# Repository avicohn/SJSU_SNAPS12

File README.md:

SJSU_SNAPS12
============

Nanosatellite System Software developed by the 2012 - 2013 SJSU SNAPS team in collaboration with NASA Ames

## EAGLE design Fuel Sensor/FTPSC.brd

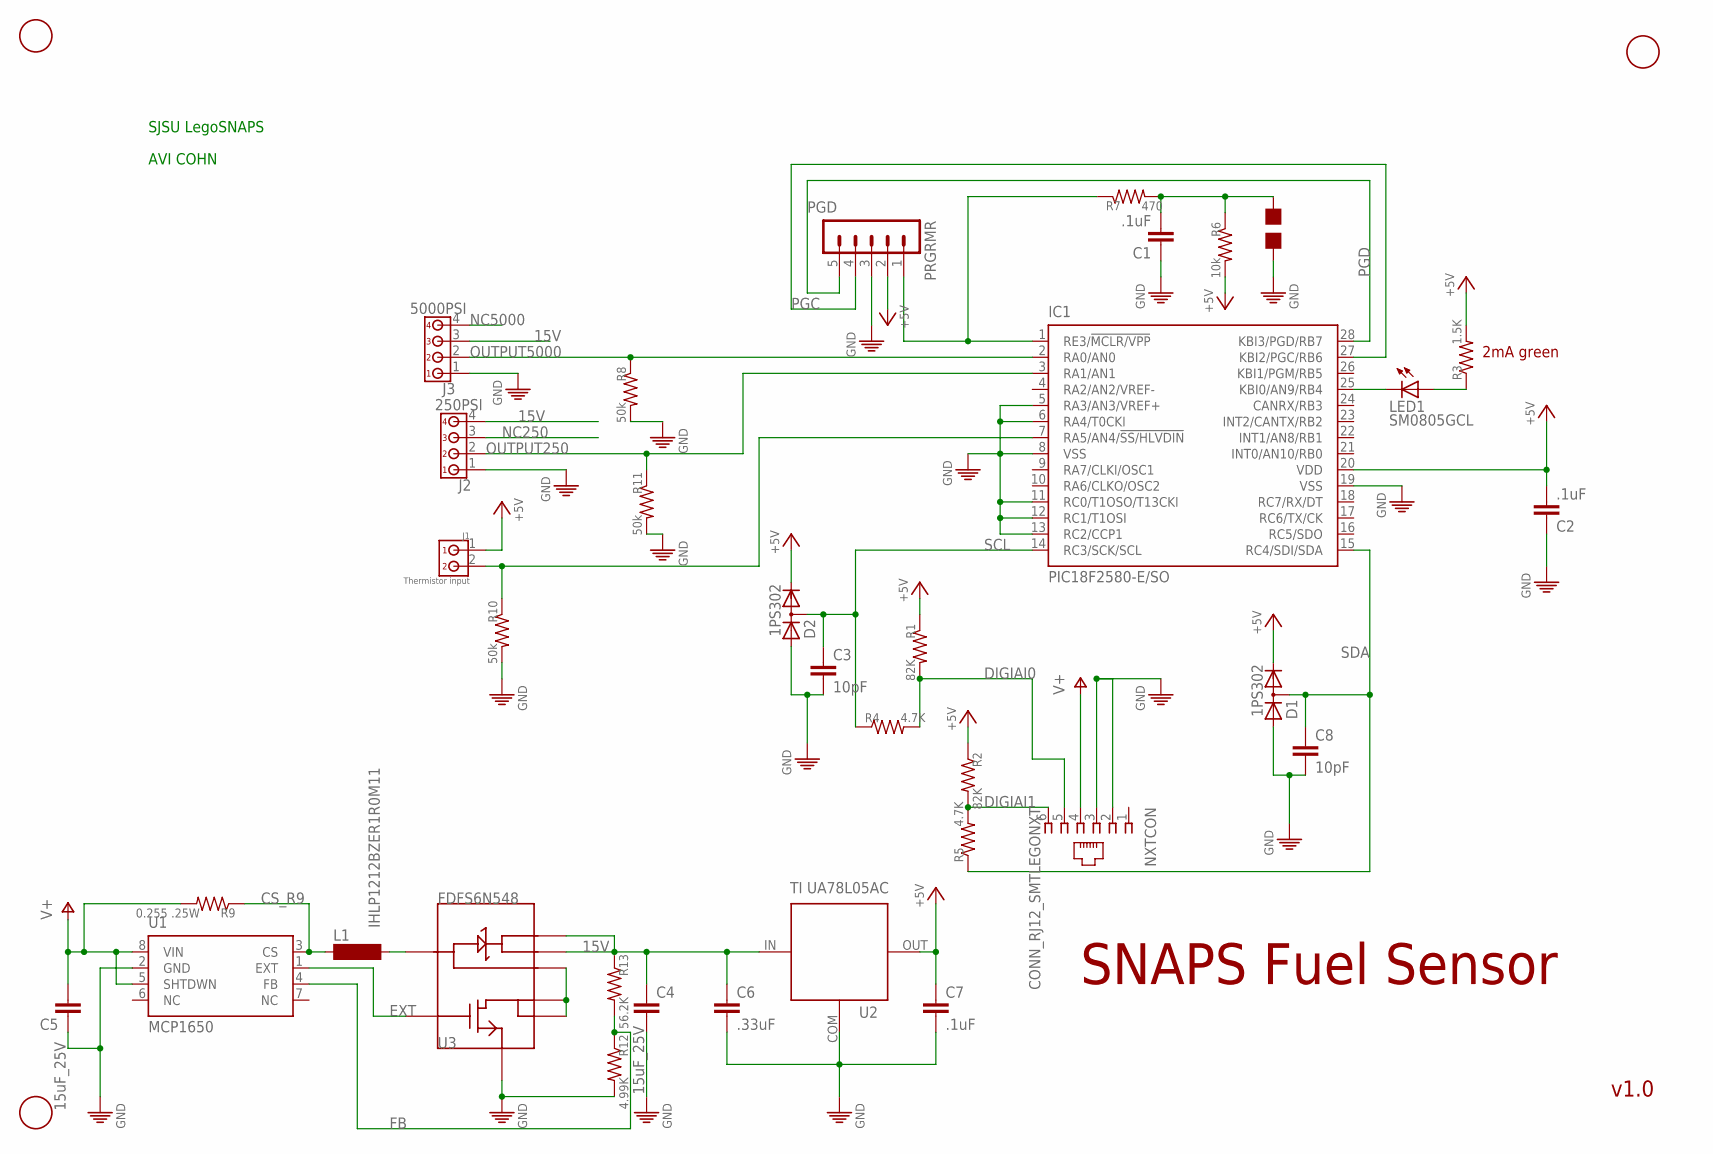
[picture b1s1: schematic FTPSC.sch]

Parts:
C1, C2, C7: .1uF; RCL_C0805
C3, C8: 10pF; RCL_C0805
C4, C5: 15uF_25V; RCL_C0805
C6: .33uF; RCL_C0805
D1, D2: 1PS302; SC70-3-R
IC1: PIC18F2580-E/SO; SO28W
J1: Thermistor input; CON-MOLEX_22-23-2021
J2: 250PSI; CON-MOLEX_22-23-2041
J3: 5000PSI; CON-MOLEX_22-23-2041
L1: IHLP1212BZER1R0M11; MS42
LED1: SM0805GCL; D0805
NXTCON: CONN_RJ12_SMTLEGONXT; NXTCONN
PRGRMR: CONN_5-PIN
R1, R2: 82K; RCL_M0805
R3: 1.5K; RCL_M0805
R4, R5: 4.7K; RCL_M0805
R6: 10k; RCL_M0805
R7: 470; RCL_M0805
R8, R10, R11: 50k; RCL_M0805
R9: 0.255 .25W; RCL_M0805
R12: 4.99K; RCL_M0805
R13: 56.2K; RCL_M0805
T1: PAD-PAIR; P0805
U1: MCP1650; SOP-08
U2: TI UA78L05AC; SOT-89
U3: FDFS6N548; SO8
U$1, U$2, U$3: FIDUCIAL; FIDUCIAL_1MM

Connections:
15V: C4.1, C6.1, J2.4, J3.3, R13.1, U2.IN, U3.7 (C), U3.8 (C)
+5V: C2.2, C7.1, D1.2 (C), D2.2 (C), IC1.20 (VDD), J1.1, PRGRMR.2, R1.1, R2.1, R3.2, R6.2, U2.OUT
CS_R9: L1.1, R9.1, U1.3 (CS)
DIGIAI0: NXTCON.5, R1.2, R4.2
DIGIAI1: NXTCON.6, R2.2, R5.2
EXT: U1.1 (EXT), U3.4 (G)
FB: R12.1, R13.2, U1.4 (FB)
GND: C1.1, C2.1, C3.2, C4.2, C5.1, C6.2, C7.2, C8.2, D1.1 (A), D2.1 (A), IC1.5 (RA3/AN3/VREF+), IC1.6 (RA4/T0CKI), IC1.8 (VSS), IC1.11 (RC0/T1OSO/T13CKI), IC1.12 (RC1/T1OSI), IC1.13 (RC2/CCP1), IC1.19 (VSS), J2.1, J3.1, NXTCON.2, NXTCON.3, PRGRMR.3, R8.2, R10.2, R11.2, R12.2, T1.1, U1.2 (GND), U2.COM, U3.3 (S)
unnamed: IC1.1 (RE3/!MCLR/VPP), PRGRMR.1, R7.1
unnamed: IC1.25 (KBI0/AN9/RB4), LED1.C
unnamed: LED1.A, R3.1
unnamed: C1.2, R6.1, R7.2, T1.2
unnamed: L1.2, U3.1 (A)
unnamed: IC1.7 (RA5/AN4/!SS/HLVDIN), J1.2, R10.1
unnamed: U3.2 (A), U3.5 (D), U3.6 (D)
NC250: J2.3
NC5000: J3.4
OUTPUT250: IC1.3 (RA1/AN1), J2.2, R11.1
OUTPUT5000: IC1.2 (RA0/AN0), J3.2, R8.1
PGC: IC1.27 (KBI2/PGC/RB6), PRGRMR.4
PGD: IC1.28 (KBI3/PGD/RB7), PRGRMR.5
SCL: C3.1, D2.3 (AC), IC1.14 (RC3/SCK/SCL), R4.1
SDA: C8.1, D1.3 (AC), IC1.15 (RC4/SDI/SDA), R5.1
V+: C5.2, NXTCON.4, R9.2, U1.5 (SHTDWN), U1.8 (VIN)

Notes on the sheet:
SNAPS Fuel Sensor
v1.0
2mA green
SJSU LegoSNAPS
AVI COHN

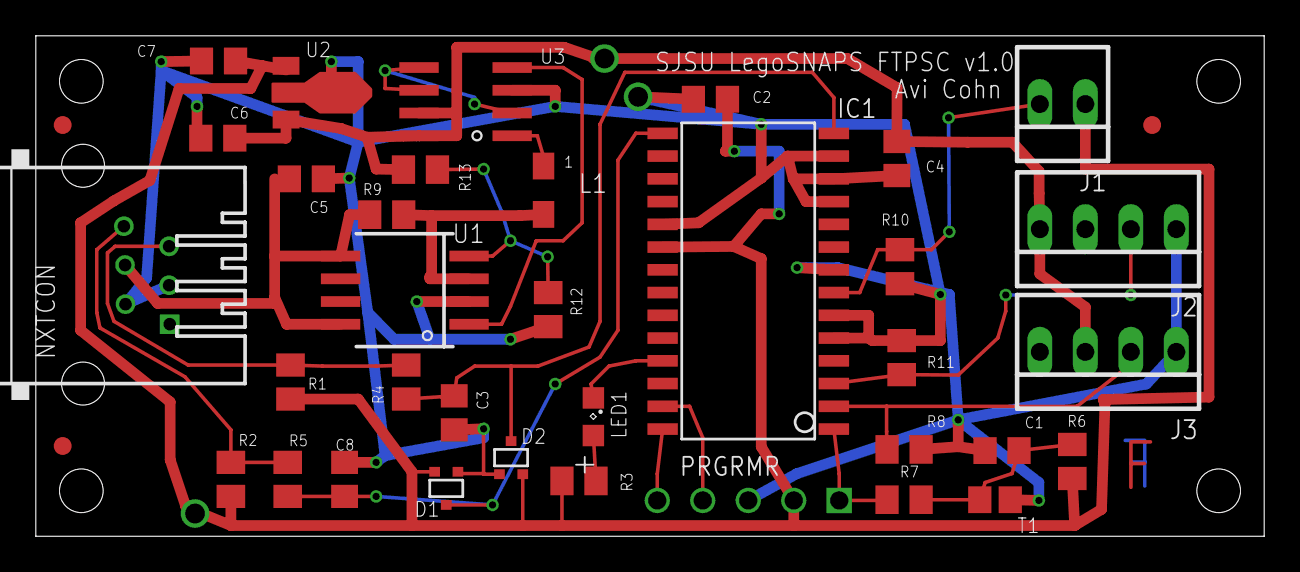
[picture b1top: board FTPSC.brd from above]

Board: 2 copper layers, 68.6 x 27.9 mm, 38 parts (0 on the bottom side), 22 nets.

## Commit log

2013-07-25 Initial commit of all code files in Spring 2013 Deliverables folder
